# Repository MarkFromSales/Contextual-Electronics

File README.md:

# Contextual-Electronics
Projects associated with my www.ContextualElectronics.com learning

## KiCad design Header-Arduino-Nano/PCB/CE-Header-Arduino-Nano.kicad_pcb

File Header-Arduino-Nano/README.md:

# CE-Header-Arduino-Nano
Connecting to an Arduino Nano using the CE Header

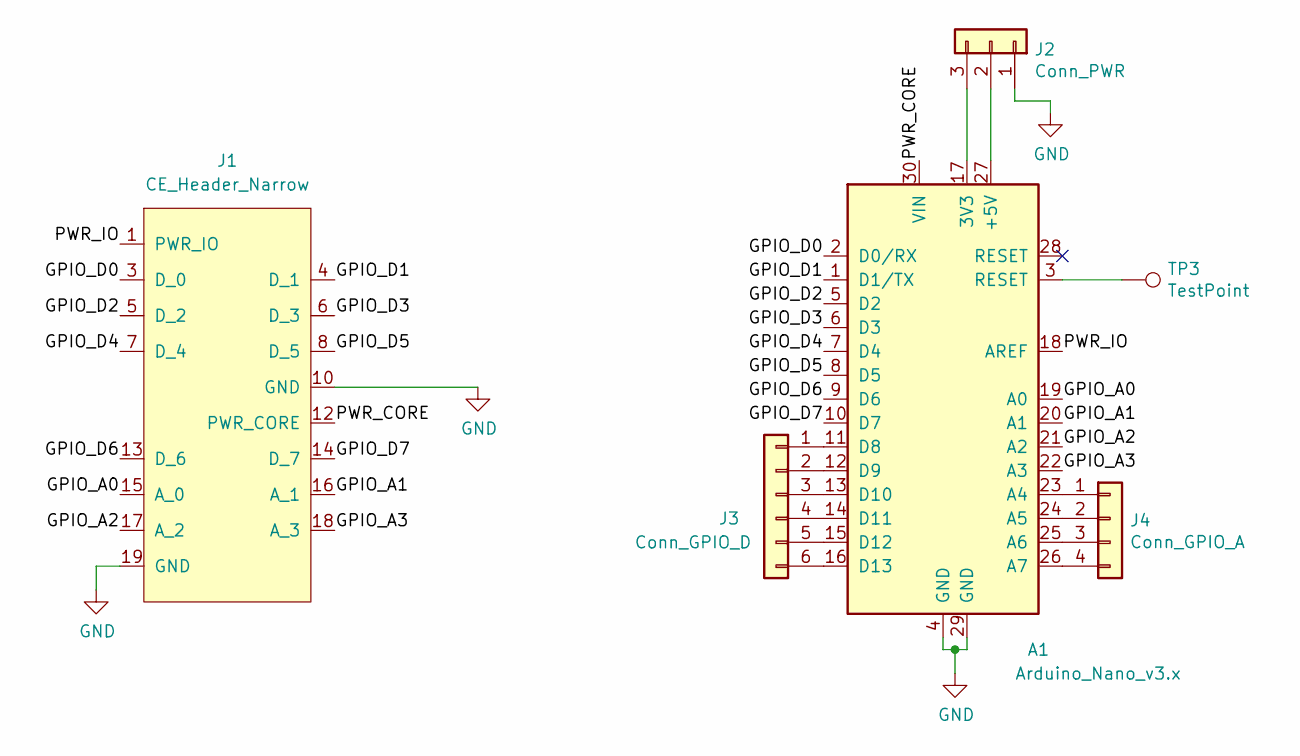
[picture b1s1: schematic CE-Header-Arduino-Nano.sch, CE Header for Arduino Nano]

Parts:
A1: Arduino_Nano_v3.x; Arduino_Nano
J1: CE_Header_Narrow; PinHeader_2x10_P2.54mm_Vertical
J2: Conn_PWR; PinHeader_1x03_P2.54mm_Vertical
J3: Conn_GPIO_D; PinHeader_1x06_P2.54mm_Vertical
J4: Conn_GPIO_A; PinHeader_1x04_P2.54mm_Vertical
TP3: TestPoint; TestPoint_Pad_D1.5mm

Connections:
/GPIO_A0: A1.19 (A0), J1.15 (A_0)
/GPIO_A1: A1.20 (A1), J1.16 (A_1)
/GPIO_A2: A1.21 (A2), J1.17 (A_2)
/GPIO_A3: A1.22 (A3), J1.18 (A_3)
/GPIO_D0: A1.2 (D0/RX), J1.3 (D_0)
/GPIO_D1: A1.1 (D1/TX), J1.4 (D_1)
/GPIO_D2: A1.5 (D2), J1.5 (D_2)
/GPIO_D3: A1.6 (D3), J1.6 (D_3)
/GPIO_D4: A1.7 (D4), J1.7 (D_4)
/GPIO_D5: A1.8 (D5), J1.8 (D_5)
/GPIO_D6: A1.9 (D6), J1.13 (D_6)
/GPIO_D7: A1.10 (D7), J1.14 (D_7)
/PWR_CORE: A1.30 (VIN), J1.12 (PWR_CORE)
/PWR_IO: A1.18 (AREF), J1.1 (PWR_IO)
GND: A1.4 (GND), A1.29 (GND), J1.10 (GND), J1.19 (GND), J2.1
unnamed: A1.3 (RESET), TP3.1
unnamed: A1.11 (D8), J3.1
unnamed: A1.12 (D9), J3.2
unnamed: A1.13 (D10), J3.3
unnamed: A1.14 (D11), J3.4
unnamed: A1.15 (D12), J3.5
unnamed: A1.16 (D13), J3.6
unnamed: A1.17 (3V3), J2.3
unnamed: A1.23 (A4), J4.1
unnamed: A1.24 (A5), J4.2
unnamed: A1.25 (A6), J4.3
unnamed: A1.26 (A7), J4.4
unnamed: A1.27 (+5V), J2.2

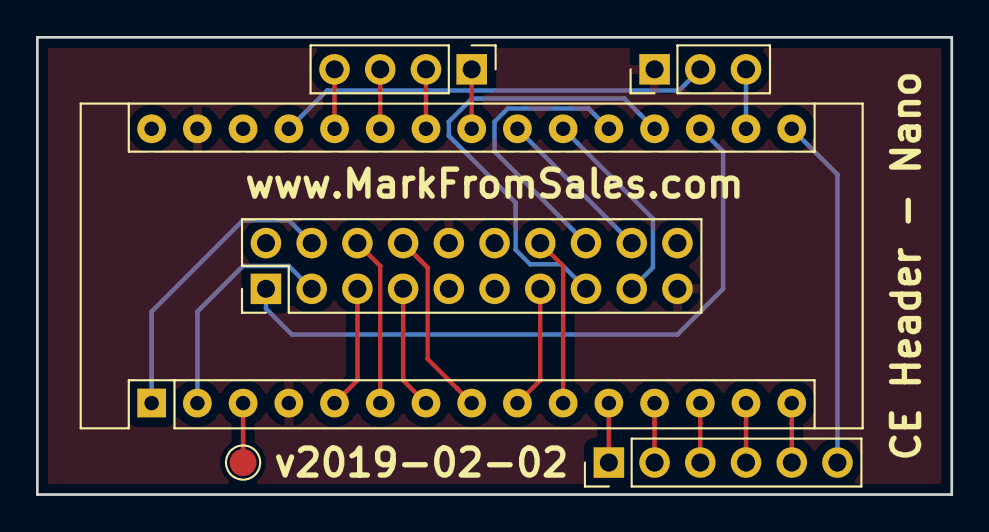
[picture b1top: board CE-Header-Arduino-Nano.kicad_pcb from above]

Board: 2 copper layers, 50.8 x 25.4 mm, 6 parts (0 on the bottom side), 28 nets.

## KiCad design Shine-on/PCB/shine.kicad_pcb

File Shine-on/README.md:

# CE-Shine-on
Shine-on project from www.contextualelectronics.com

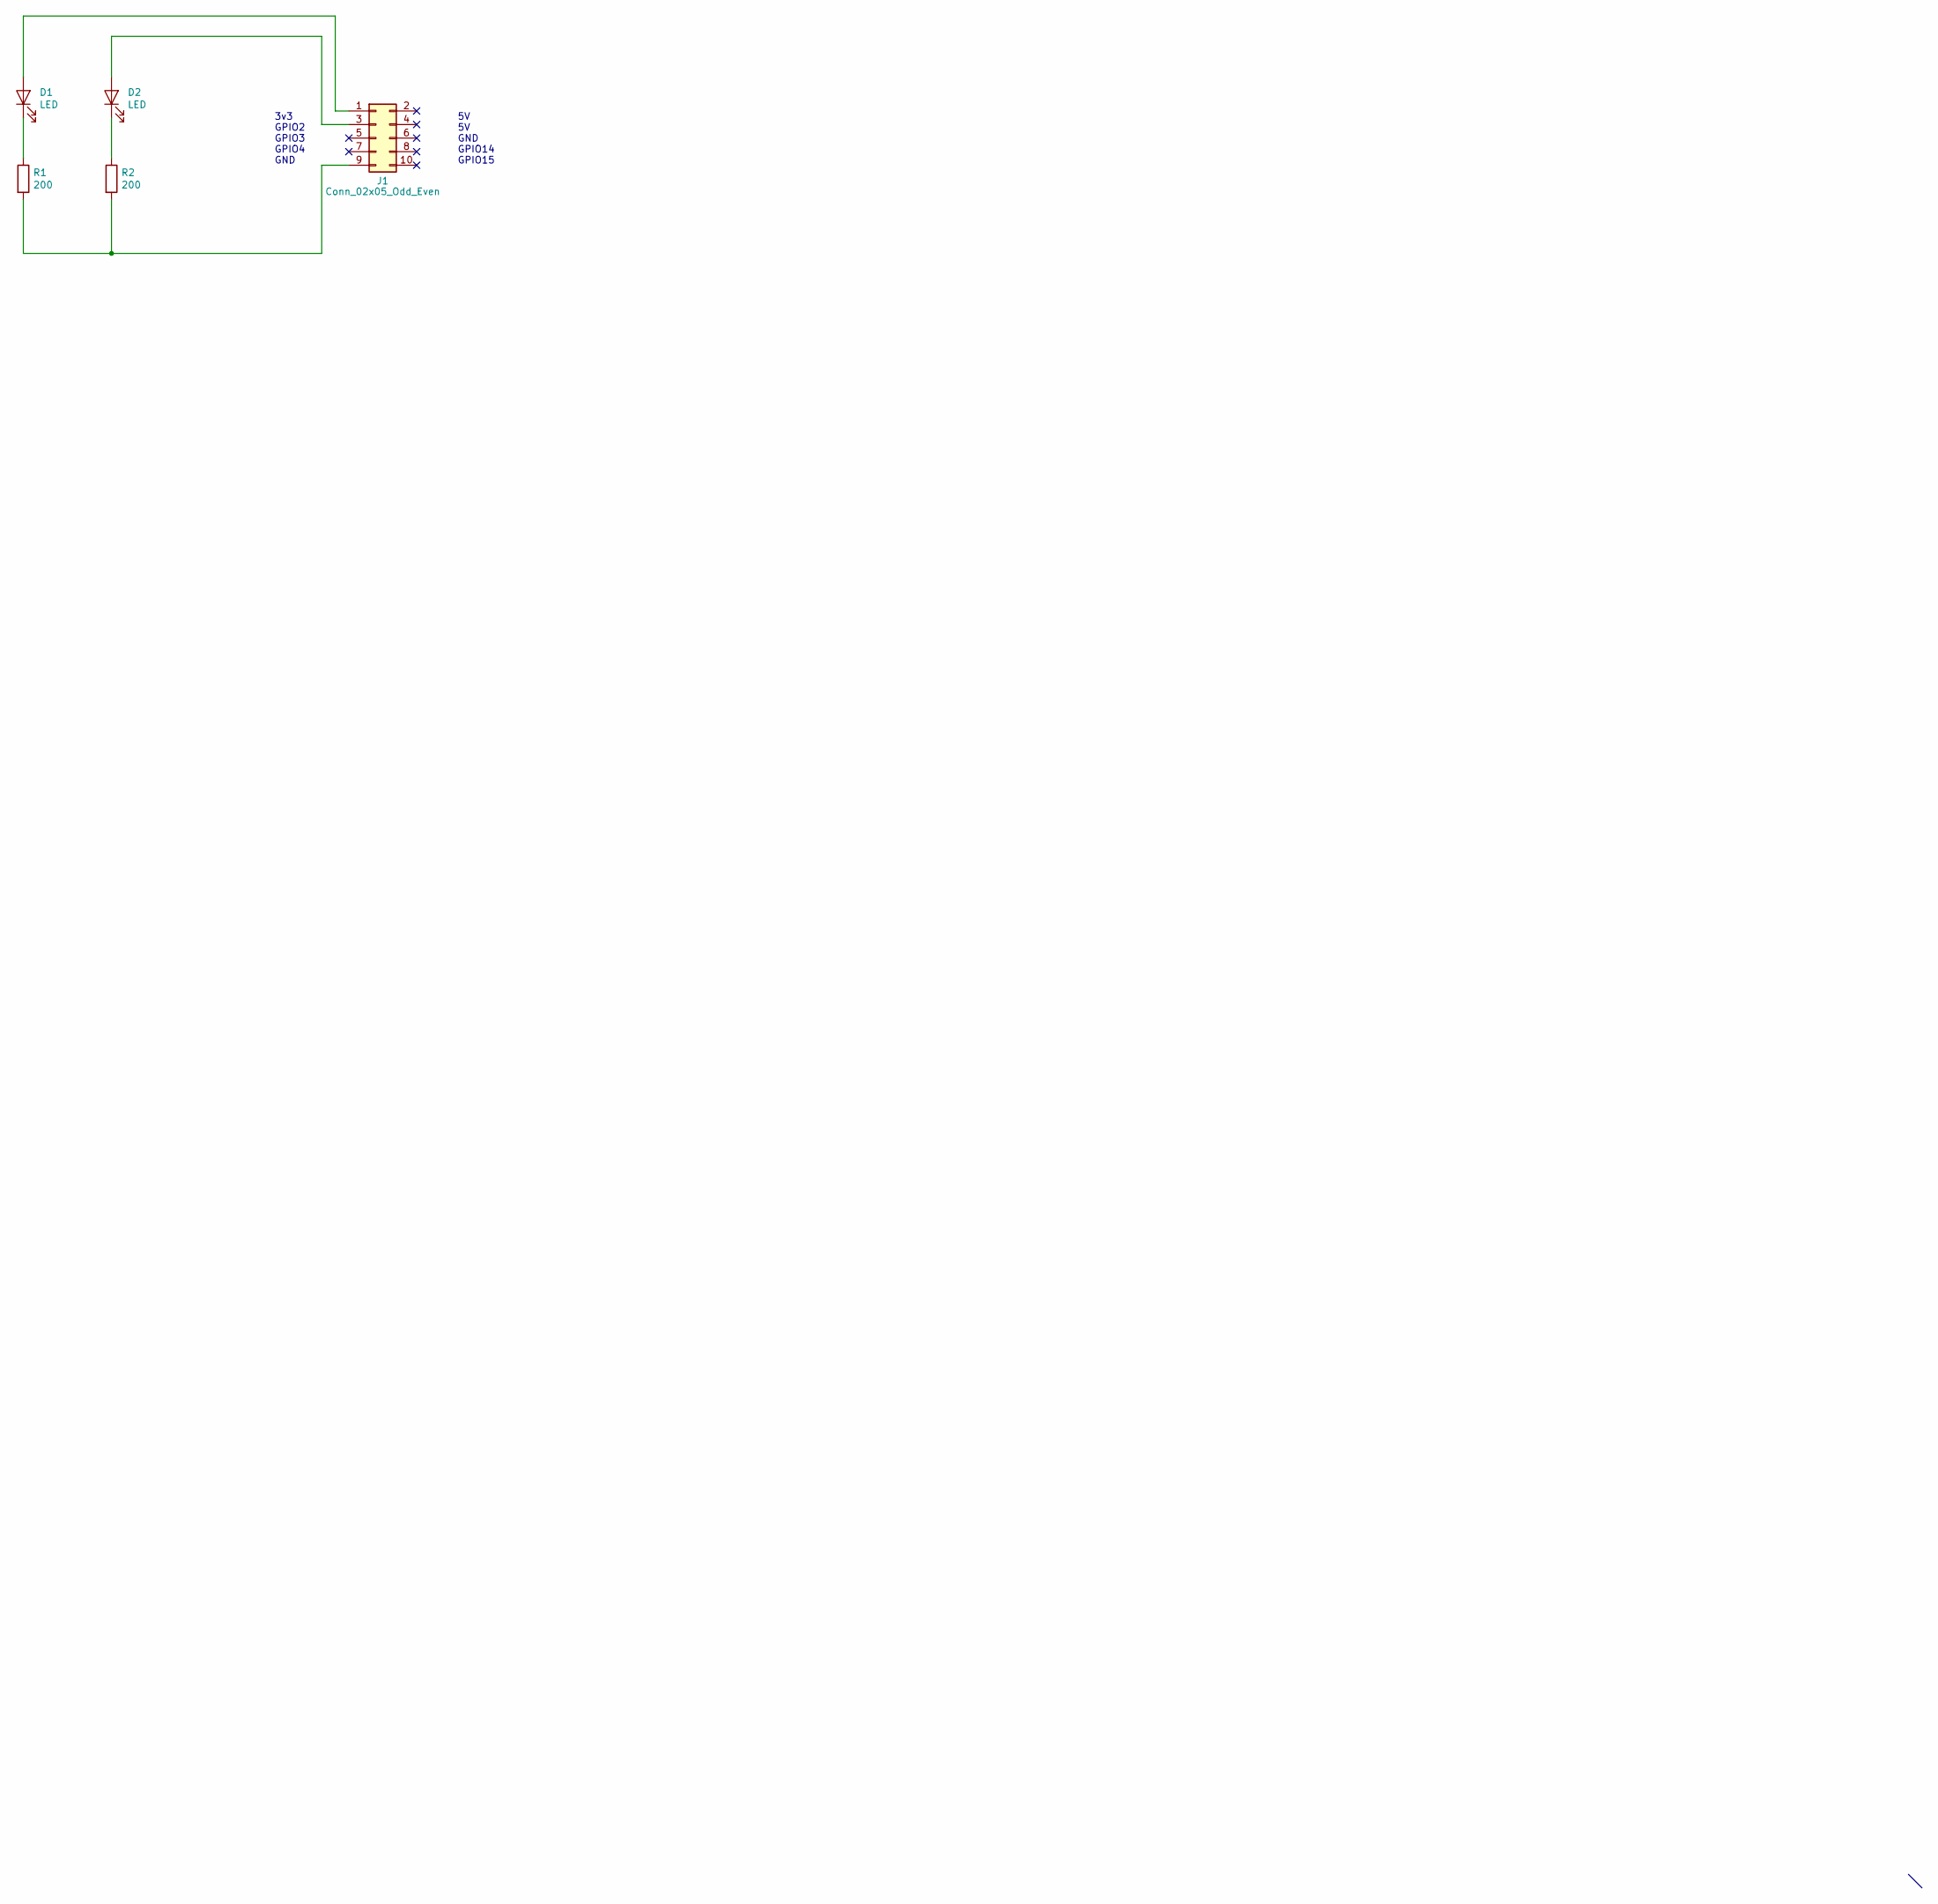
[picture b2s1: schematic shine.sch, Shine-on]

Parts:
D1, D2: LED; LED_1206_3216Metric_Pad1.42x1.75mm_HandSolder
J1: Conn_02x05_Odd_Even; PinHeader_2x05_P2.54mm_Vertical
R1, R2: 200; R_1206_3216Metric_Pad1.42x1.75mm_HandSolder

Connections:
unnamed: D1.1 (K), R1.1
unnamed: D1.2 (A), J1.1
unnamed: D2.1 (K), R2.1
unnamed: D2.2 (A), J1.3
unnamed: J1.9, R1.2, R2.2

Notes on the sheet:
3v3 GPIO2 GPIO3 GPIO4 GND
5V 5V GND GPIO14 GPIO15

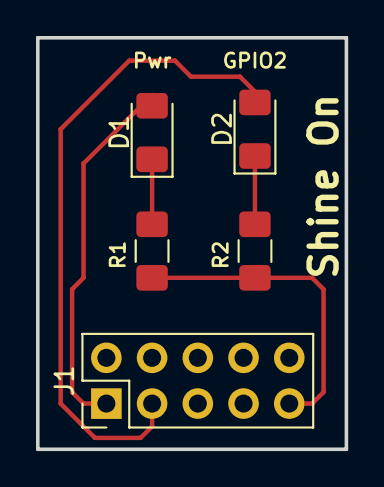
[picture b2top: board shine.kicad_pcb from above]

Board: 2 copper layers, 17.1 x 22.9 mm, 5 parts (0 on the bottom side), 5 nets.

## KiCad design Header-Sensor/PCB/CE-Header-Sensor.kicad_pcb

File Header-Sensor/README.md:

# CE-Header-Sensor
Contextual Electronics header with Sensor board

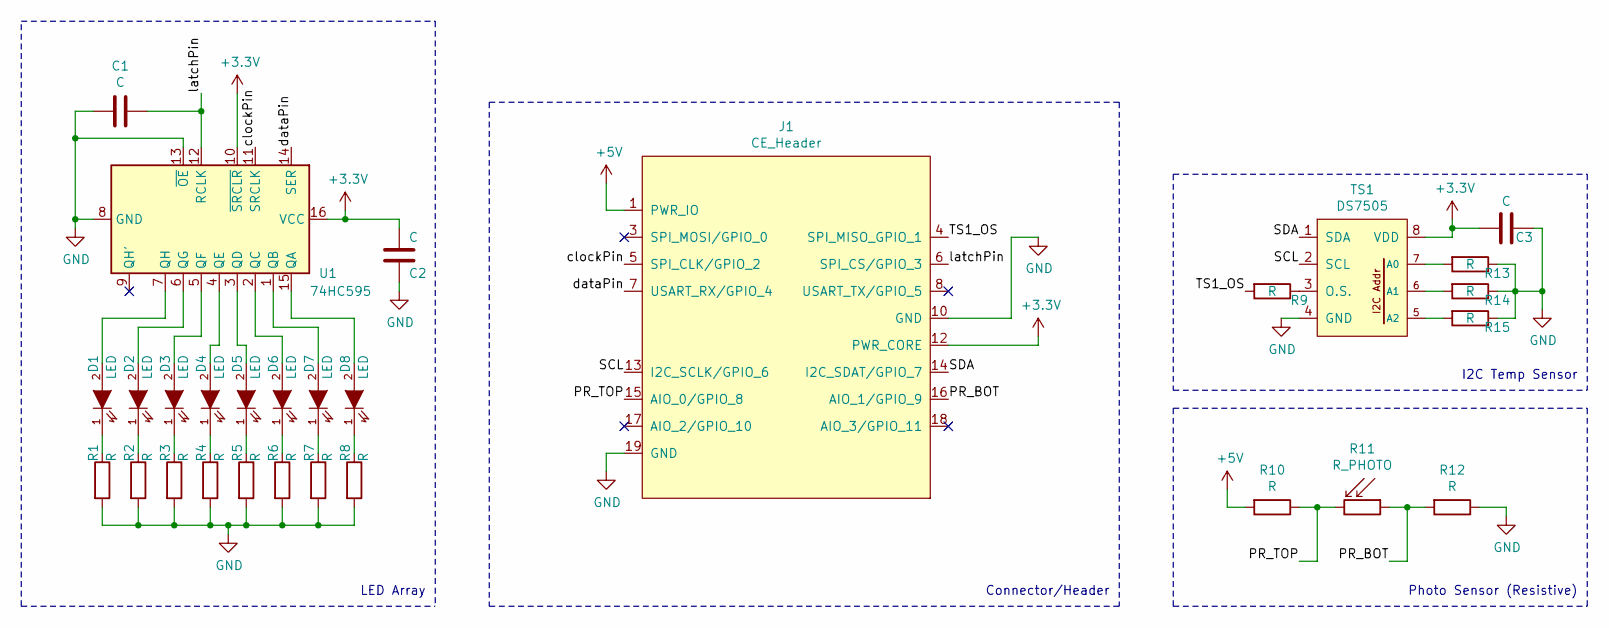
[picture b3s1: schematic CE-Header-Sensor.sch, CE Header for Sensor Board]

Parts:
C1, C2, C3: C; C_0805_2012Metric_Pad1.15x1.40mm_HandSolder
D1, D2, D3, D4, D5, D6, D7, D8: LED; LED_0805_2012Metric_Pad1.15x1.40mm_HandSolder
J1: CE_Header
R1, R2, R3, R4, R5, R6, R7, R8, R9, R10, R12, R13, R14, R15: R; R_0805_2012Metric_Pad1.15x1.40mm_HandSolder
R11: R_PHOTO; CP_Radial_Tantal_D5.5mm_P5.00mm; MPN PDV-P8103
TS1: DS7505; SOIC-8_W3.9mm
U1: 74HC595; SOIC-16_W3.90mm

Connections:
+3V3: C2.1, C3.1, J1.12 (PWR_CORE), TS1.8 (VDD), U1.10 (~SRCLR), U1.16 (VCC)
+5V: J1.1 (PWR_IO), R10.2
/PR_BOT: J1.16 (AIO_1/GPIO_9), R11.1, R12.2
/PR_TOP: J1.15 (AIO_0/GPIO_8), R10.1, R11.2
/SCL: J1.13 (I2C_SCLK/GPIO_6), TS1.2 (SCL)
/SDA: J1.14 (I2C_SDAT/GPIO_7), TS1.1 (SDA)
/TS1_OS: J1.4 (SPI_MISO_GPIO_1), R9.2
/clockPin: J1.5 (SPI_CLK/GPIO_2), U1.11 (SRCLK)
/dataPin: J1.7 (USART_RX/GPIO_4), U1.14 (SER)
/latchPin: C1.2, J1.6 (SPI_CS/GPIO_3), U1.12 (RCLK)
GND: C1.1, C2.2, C3.2, J1.10 (GND), J1.19 (GND), R1.2, R2.2, R3.2, R4.2, R5.2, R6.2, R7.2, R8.2, R12.1, R13.1, R14.1, R15.1, TS1.4 (GND), U1.8 (GND), U1.13 (~OE)
unnamed: D1.1 (K), R1.1
unnamed: D1.2 (A), U1.7 (QH)
unnamed: D2.1 (K), R2.1
unnamed: D2.2 (A), U1.6 (QG)
unnamed: D3.1 (K), R3.1
unnamed: D3.2 (A), U1.5 (QF)
unnamed: D4.1 (K), R4.1
unnamed: D4.2 (A), U1.4 (QE)
unnamed: D5.1 (K), R5.1
unnamed: D5.2 (A), U1.3 (QD)
unnamed: D6.1 (K), R6.1
unnamed: D6.2 (A), U1.2 (QC)
unnamed: D7.1 (K), R7.1
unnamed: D7.2 (A), U1.1 (QB)
unnamed: D8.1 (K), R8.1
unnamed: D8.2 (A), U1.15 (QA)
unnamed: R9.1, TS1.3 (O.S.)
unnamed: R13.2, TS1.7 (A0)
unnamed: R14.2, TS1.6 (A1)
unnamed: R15.2, TS1.5 (A2)

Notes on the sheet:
I2C Temp Sensor
Photo Sensor (Resistive)
LED Array
Connector/Header

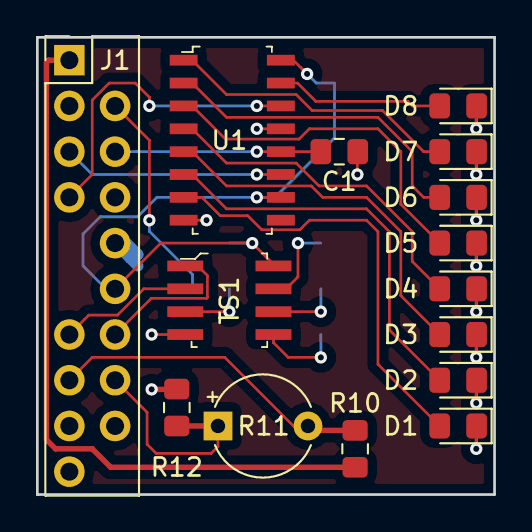
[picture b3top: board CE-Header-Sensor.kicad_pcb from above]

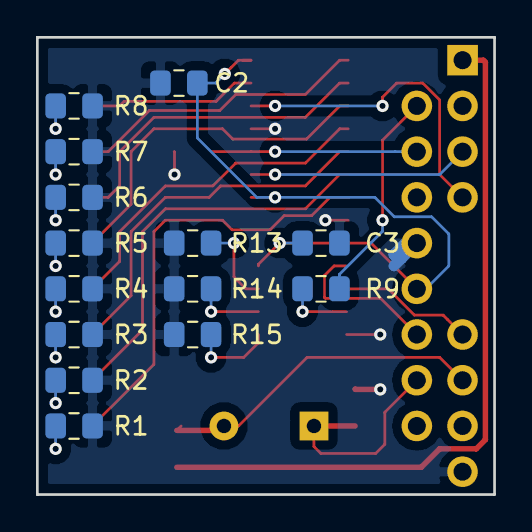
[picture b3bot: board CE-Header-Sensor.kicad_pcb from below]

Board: 2 copper layers, 25.4 x 25.4 mm, 29 parts (14 on the bottom side), 31 nets.

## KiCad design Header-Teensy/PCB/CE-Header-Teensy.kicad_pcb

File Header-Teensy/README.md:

# CE-Header-Teensy
CE Header for Teensy 3.x

From project on www.contextualelectronics.com

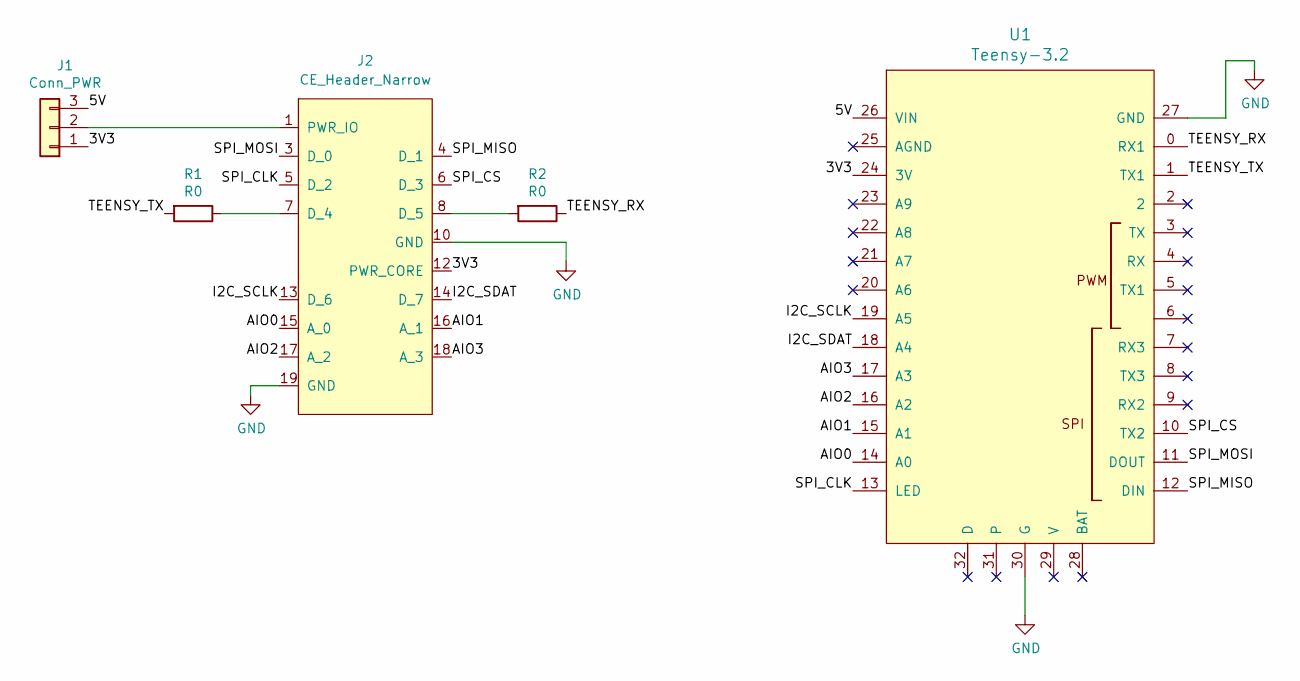
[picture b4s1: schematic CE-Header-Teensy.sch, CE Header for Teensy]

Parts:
J1: Conn_PWR; PinHeader_1x03_P2.54mm_Vertical
J2: CE_Header_Narrow; PinHeader_2x10_P2.54mm_Vertical
R1, R2: R0; R_1206_3216Metric_Pad1.42x1.75mm_HandSolder
U1: Teensy-3.2; Teensy-32-Mirrored

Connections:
/3V3: J1.1, J2.12 (PWR_CORE), U1.24 (3V)
/5V: J1.3, U1.26 (VIN)
/AIO0: J2.15 (A_0), U1.14 (A0)
/AIO1: J2.16 (A_1), U1.15 (A1)
/AIO2: J2.17 (A_2), U1.16 (A2)
/AIO3: J2.18 (A_3), U1.17 (A3)
/I2C_SCLK: J2.13 (D_6), U1.19 (A5)
/I2C_SDAT: J2.14 (D_7), U1.18 (A4)
/SPI_CLK: J2.5 (D_2), U1.13 (LED)
/SPI_CS: J2.6 (D_3), U1.10 (TX2)
/SPI_MISO: J2.4 (D_1), U1.12 (DIN)
/SPI_MOSI: J2.3 (D_0), U1.11 (DOUT)
/TEENSY_RX: R2.1, U1.0 (RX1)
/TEENSY_TX: R1.2, U1.1 (TX1)
GND: J2.10 (GND), J2.19 (GND), U1.27 (GND), U1.30 (G)
unnamed: J1.2, J2.1 (PWR_IO)
unnamed: J2.7 (D_4), R1.1
unnamed: J2.8 (D_5), R2.2

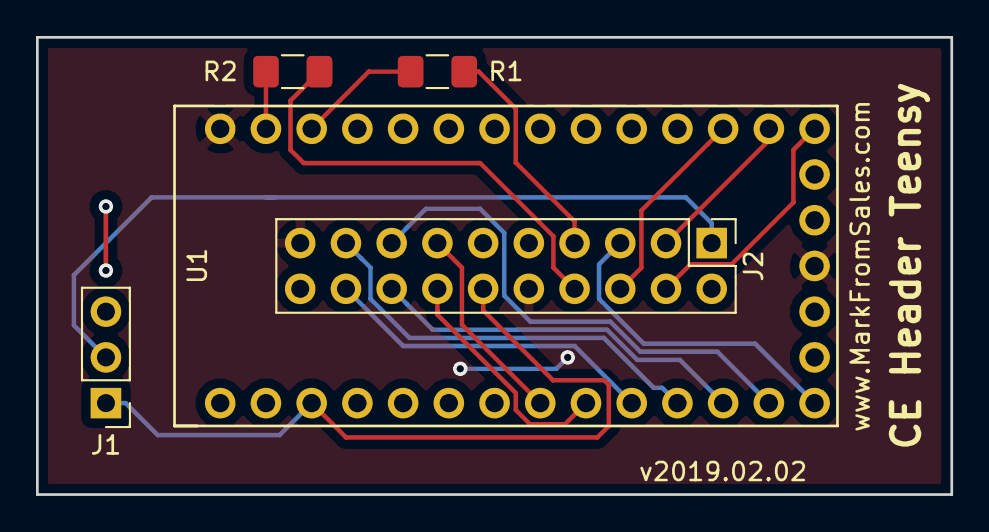
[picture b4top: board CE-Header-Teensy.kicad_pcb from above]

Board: 2 copper layers, 50.8 x 25.4 mm, 5 parts (0 on the bottom side), 18 nets.

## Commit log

2019-02-13 Updated structure
